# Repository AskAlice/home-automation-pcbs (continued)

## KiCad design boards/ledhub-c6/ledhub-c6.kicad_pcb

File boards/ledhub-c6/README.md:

# ledhub-c6 — all-in-one display LED controller (80 × 50 mm)

ESP32-C6-WROOM-1 based LED controller with 2.8" ILI9341 TFT, EC11 rotary
encoder, 5-way ADC-ladder nav buttons, INMP441 I2S microphone, SHT31 +
BH1750 environmental sensors, LD2450 mmWave radar header, and a 5 V
level-shifted WS2812 output (74AHCT125 + 470 Ω).

**Primary firmware: WLED 0.15+** (ESP32-C6 supported since 0.15) with
`firmware/wled-usermod-ledhub/`. ESPHome is also possible — see
`esphome/ledhub-c6.yaml` (draft covering display, encoder, ADC buttons,
I2S mic, I2C sensors, LD2450 UART, RMT LED strip).

License: MIT. KiCad 8 project, generated by `gen_ledhub_c6.py`
(`python3 gen_ledhub_c6.py`; exits non-zero on any validation problem).

## Features

- USB-C power + native USB-Serial-JTAG flashing (GPIO12/13 via 22 Ω,
  5.1 kΩ CC pull-downs)
- AP2112K-3.3 LDO (VBUS → +3V3), logic 5 V rail `+5V` from VBUS via R20 0R
- Separate `LED_5V` input terminal (J4, 5.08 mm) powering the LED strip
  only; LED data out on J3 (LED_5V / DATA / GND)
- 74AHCT125 (U5, SOIC-14, VCC=+5V, 1OE=GND) level-shifts GPIO3 → LED_DATA
  through R19 470 Ω
- Antenna keepout (no copper, all layers) at the module antenna end

## Frozen pin map (firmware contract — do not change)

| Function | ESP32-C6 GPIO |
|---|---|
| TFT SCK / MOSI / CS / DC / RST / BL | 6 / 7 / 5 / 4 / 1 / 2 |
| Encoder A / B (common = GND; push NC) | 15 / 16 |
| Nav button ladder (ADC1_CH0) | 0 |
| INMP441 I2S SCK / WS / SD (L/R=GND) | 17 / 18 / 19 |
| I2C SDA / SCL (SHT31 + BH1750, 4.7 kΩ) | 20 / 21 |
| LD2450: MCU_RX ← radar TX / MCU_TX → radar RX | 22 / 23 |
| WS2812 data (via 74AHCT125) | 3 |
| USB D− / D+ | 12 / 13 |
| UART0 TX0 / RX0 (prog header J5) | 16 / 17 |
| BOOT button / EN reset | 9 / EN |

GPIO 8/9/12/13/26–30 avoided for general I/O (strapping/USB/flash).

## GPIO16/17 double-assignment — R16/R17 0Ω links

The frozen pin map uses GPIO16 for both ENC_B and UART0 TX0, and GPIO17
for both I2S_SCK and UART0 RX0. R16 (ENC_B↔TX0) and R17 (I2S_SCK↔RX0)
are 0 Ω links, fitted by default. **Flash firmware via native USB-C**
(USB-Serial-JTAG on GPIO12/13) — no UART adapter needed. For classic
UART0 flashing via J5, remove R16/R17 (or accept encoder/I2S contention
while the programmer is attached). Documented on the schematic (title
block notes) and here.

## ADC button ladder (GPIO0, 12-bit)

Topology: +3V3 —10 kΩ (R11)— GPIO0 node; each button shorts the node to
GND through its ladder resistor:

| Button | R | Voltage | ADC (0–4095) | Threshold band |
|---|---|---|---|---|
| UP | 0 Ω (R12) | 0.000 V | 0 | < 369 |
| DN | 2.2 kΩ (R13) | 0.595 V | 738 | 369–1023 |
| LF | 4.7 kΩ (R14) | 1.055 V | 1308 | 1023–1678 |
| RT | 10 kΩ (R15) | 1.650 V | 2048 | 1678–2430 |
| OK | 22 kΩ (R18) | 2.269 V | 2813 | 2430–3454 |
| none | — | 3.300 V | 4095 | > 3454 |

## BOM (bom_lcsc.csv; LCSC numbers verified in-stock via jlcsearch, 2026-08)

| Ref | Value | Footprint | LCSC # | MPN | Qty |
|---|---|---|---|---|---|
| U1 | ESP32-C6-WROOM-1 | custom 18×25.5 mm | C5366877 | ESP32-C6-WROOM-1-N8 | 1 |
| X1 | USB-C 16P receptacle | USB_C_Receptacle_USB2.0_16P | C165948 | TYPE-C-31-M-12 | 1 |
| U2 | INMP441 (bottom port) | custom LGA-9 | — (not stocked) | INMP441ACEZ-R7 | 1 |
| U3 | SHT31 | custom DFN-8 2.5×2.5 | C80862 | SHT31-DIS-B2.5kS | 1 |
| U4 | BH1750 | custom WSOF-6I | C78960 | BH1750FVI-TR | 1 |
| U5 | 74AHCT125 | SOIC-14 | C842299 | 74AHCT125S14-13 | 1 |
| U6 | AP2112K-3.3 | SOT-23-5 | C51118 | AP2112K-3.3TRG1 | 1 |
| ENC1 | EC11 encoder | custom THT | C370970 | EC11E15244G1 | 1 |
| R1,R2,R14 | 4.7 kΩ | 0603 | C23162 | 0603WAF4701T5E | 3 |
| R13 | 2.2 kΩ | 0603 | C4190 | 0603WAF2201T5E | 1 |
| R7,R10,R11,R15 | 10 kΩ | 0603 | C25804 | 0603WAF1002T5E | 4 |
| R18 | 22 kΩ | 0603 | C31850 | 0603WAF2202T5E | 1 |
| R3,R4 | 5.1 kΩ | 0603 | C23186 | 0603WAF5101T5E | 2 |
| R5,R6 | 22 Ω | 0603 | C22926 | 0603WAF220JT5E | 2 |
| R9 | 100 Ω | 0603 | C22775 | 0603WAF1000T5E | 1 |
| R19 | 470 Ω | 0603 | C23179 | 0603WAF4700T5E | 1 |
| R8 | 1 kΩ | 0603 | C21190 | 0603WAF1001T5E | 1 |
| R12,R16,R17,R20,R21 | 0 Ω link | 0603 | C21189 | 0603WAF0000T5E | 5 |
| C1,C2,C8 | 10 µF | 0603 | C15849 | CL10A106KP8NNNC | 3 |
| C3–C7,C9,C10 | 100 nF | 0603 | C14663 | 0603B104K500NT | 7 |
| D1 | red LED | 0603 | C2286 | LTST-C190KRKT | 1 |
| BT1,BT2,BT_UP/DN/LF/RT/OK | tactile 6×6 | custom SMD | C318884 | TS-1187A-B-A-B | 7 |
| J1 | 2×7 header (TFT) | PinHeader_2x07 | C492424 | PZ254V-12-14P | 1 |
| J2 | 1×5 header (LD2450) | PinHeader_1x05 | C492404 | PZ254V-11-05P | 1 |
| J5 | 1×4 header (prog) | PinHeader_1x04 | C2691448 | PZ254V-11-04P | 1 |
| J3 | screw terminal 3P | custom KF128-5.08 | C474953 | KF128-5.08-3P-AA | 1 |
| J4 | screw terminal 2P | custom KF128-5.08 | C474952 | KF128-5.08-2P-AA | 1 |
| (on J1) | 2.8" ILI9341 TFT module | module | — | ILI9341-2.8-SPI | 1 |
| (on J2) | LD2450 radar module | module | — | HLK-LD2450 | 1 |

## Assembly / mechanical notes

- **INMP441 (U2)** is a bottom-port LGA (4.72×3.76 mm): the PCB has an
  Ø0.8 mm sound-port hole under the package. Reflow strongly
  recommended; hand-soldering is hostile (no exposed pad edges). Do not
  plug the port hole with solder.
- **SHT31** footprint is the real DFN-8 2.5×2.5 mm package.
- **TFT module** on J1 (2×7 header) may overhang the board edge —
  mechanical note only; confirm clearance in the enclosure.
- EC11 switch pins are NC (push = use OK button instead).
- TFT backlight: GPIO2 via R9 100 Ω, R10 10 kΩ pull-down keeps the
  backlight off during reset.

## Routing status

Rev 1.0 ships with **no routed tracks/vias**: all nets are ratsnest
(a full-board GND pour on B.Cu plus small per-net marker pours on F.Cu
document the net set). A previous auto-routing attempt produced cross-net
collisions, so routing is deliberately deferred to interactive work in
KiCad (or a verified autorouter pass). Power rails must be routed at
≥ 0.5 mm when done. The generator self-checks pad/courtyard clearances
geometrically and the kicad-happy analyzer reports **0 cross-net
(DFM-001) violations**.

## Analyzer notes (kicad-happy triage)

- PM-002 BT1/BT2 0.75 mm from board edge: intentional (left-edge button
  column); >= 0.5 mm fab clearance held.
- TE-001 no test points: prog header J5 + module pads serve as access.
- TV-001 no thermal vias on U1 EP: EP is ground-paddle soldered;
  C6 module dissipation is modest; add via-in-pad if thermals matter.
- PU-001 SHT31 ALERT/RESET NC by design (not used).
- RS-001 +5V/LED_5V/VBUS "no declared source": rails enter via USB-C /
  screw terminals (connectors are the sources).
- DS-002: datasheets/ sync is handled by the repo-level parts pipeline.

## Flashing

1. Hold BOOT (BT2), tap EN (BT1), release BOOT → download mode.
2. `esptool.py --chip esp32c6 write_flash ...` via the USB-C port
   (native USB-Serial-JTAG), or `esphome run esphome/ledhub-c6.yaml`.
3. UART0 header J5 (+3V3/TX0/RX0/GND) only with R16/R17 removed.

**Verify all custom footprints against the manufacturer datasheets before
fabrication.** Renders: see below (`render_top.png` / `render_bottom.png`
when generated by `tools/render_pcb.py`).

## Renders

| Raytraced 3D (KiCad) | 2D layout |
|---|---|
|  |  |
|  |  |

🎬 24 real KiCad raytraced frames
stitched with ffmpeg (`tools/turntable.sh`).

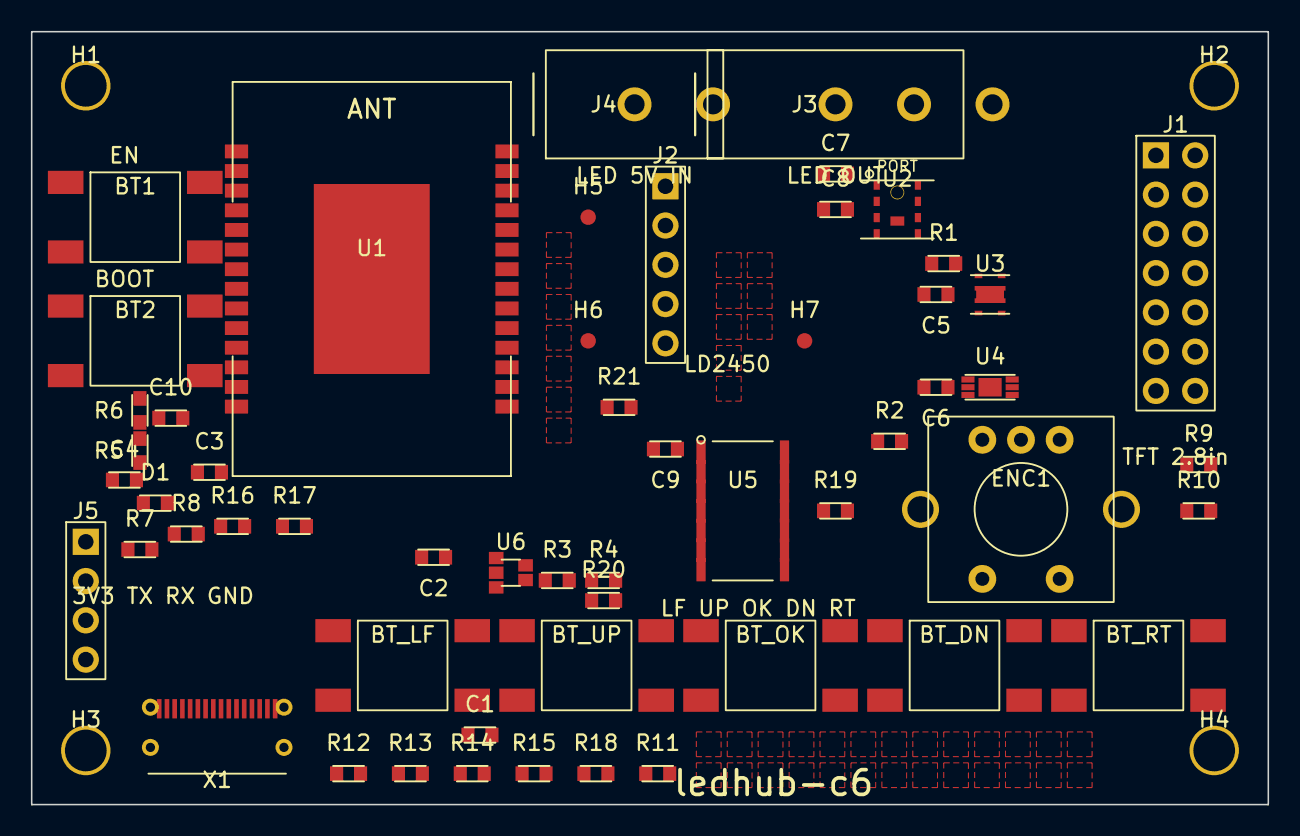
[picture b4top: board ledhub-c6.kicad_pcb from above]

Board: 2 copper layers, 80.0 x 50.0 mm, 59 parts (0 on the bottom side), 37 nets, no tracks yet.

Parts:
BT1, BT2: SW_PUSH; Tactile-6x6-SMD
BT_DN: SW_PUSH; Tactile-6x6-SMD
BT_LF: SW_PUSH; Tactile-6x6-SMD
BT_OK: SW_PUSH; Tactile-6x6-SMD
BT_RT: SW_PUSH; Tactile-6x6-SMD
BT_UP: SW_PUSH; Tactile-6x6-SMD
C1, C2, C8: 10uF; C_0603_1608Metric
C3, C4, C5, C6, C7, C9, C10: 100nF; C_0603_1608Metric
D1: LED_RED; LED_0603_1608Metric
ENC1: EC11; EC11-Encoder
H1, H2, H3, H4: MountingHole_M2.5
H5, H6, H7: Fiducial; Fiducial_1mm
J1: Conn_02x07; PinHeader_2x07_P2.54mm_Vertical
J2: Conn_01x05; PinHeader_1x05_P2.54mm_Vertical
J3: Term_3P; KF128-5.08-3P
J4: Term_2P; KF128-5.08-2P
J5: Conn_01x04; PinHeader_1x04_P2.54mm_Vertical
R1, R2, R14: 4.7k; R_0603_1608Metric
R3, R4: 5.1k; R_0603_1608Metric
R5, R6: 22R; R_0603_1608Metric
R7, R10, R11, R15: 10k; R_0603_1608Metric
R8: 1k; R_0603_1608Metric
R9: 100R; R_0603_1608Metric
R12, R16, R17, R20, R21: 0R; R_0603_1608Metric
R13: 2.2k; R_0603_1608Metric
R18: 22k; R_0603_1608Metric
R19: 470R; R_0603_1608Metric
U1: ESP32-C6-WROOM-1
U2: INMP441; INMP441-LGA9
U3: SHT31; SHT31-DFN8
U4: BH1750; BH1750-WSOF6
U5: 74AHCT125; SOIC-14_3.9x8.7mm_P1.27mm
U6: AP2112K-3.3; SOT-23-5
X1: USB_C_16P; USB_C_Receptacle_USB2.0_16P

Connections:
+3V3: C2.1, C3.1, C5.1, C6.1, C7.1, C8.1, C10.1, J1.1, J5.1, R1.1, R2.1, R7.1, R8.1, R11.1, U1.2, U2.7, U2.8, U3.5, U4.1, U4.5, U6.5
+5V: C9.1, J2.1, R20.2, U5.4, U5.10, U5.13, U5.14
BTN_ADC: R11.2, R12.1, R13.1, R14.1, R15.1, R18.1, U1.8
B_OK: BT1.1, BT1.3, BT2.1, BT2.3, BT_DN.1, BT_DN.3, BT_LF.1, BT_LF.3, BT_OK.1, BT_OK.3, BT_RT.1, BT_RT.3, BT_UP.1, BT_UP.3, R18.2
EN: C4.1, R7.2, U1.3
ENC_A: ENC1.1, U1.23
ENC_B: ENC1.3, R16.1, U1.25
GND: BT1.2, BT1.4, BT2.2, BT2.4, BT_DN.2, BT_DN.4, BT_LF.2, BT_LF.4, BT_OK.2, BT_OK.4, BT_RT.2, BT_RT.4, BT_UP.2, BT_UP.4, C1.2, C2.2, C3.2, C4.2, C5.2, C6.2, C7.2, C8.2, C9.2, C10.2, D1.2, ENC1.2, J1.2, J2.4, J2.5, J3.3, J4.2, J5.4, R3.2, R4.2, R10.2, U1.1, U1.28, U1.29, U2.4, U2.5, U2.6, U2.9, U3.2, U3.8, U3.9, U4.2, U4.3, U4.7, U5.1, U5.5, U5.7, U5.9, U5.12, U6.2, X1.1, X1.8, X1.9, X1.16, X1.S1, X1.S2, X1.S3, X1.S4
I2C_SCL: R2.2, U1.19, U3.4, U4.6
I2C_SDA: R1.2, U1.18, U3.1, U4.4
I2S_SCK: R17.1, U1.24, U2.1
I2S_SD: U1.17, U2.2
I2S_WS: U1.16, U2.3
LED1_A: D1.1, R8.2
LED_5V: J3.1, J4.1
LED_DATA: J3.2, R19.2
LED_DIN: R21.1, U1.26
LED_DINB: R21.2, U5.2
LED_PRE: R19.1, U5.3
RAD_RX: J2.2, U1.20
RAD_TX: J2.3, U1.21
RX0: J5.3, R17.2
TFT_BL: R9.1, U1.27
TFT_BLP: J1.8, R9.2, R10.1
TFT_CS: J1.3, U1.5
TFT_DC: J1.5, U1.4
TFT_MOSI: J1.6, U1.7
TFT_RST: J1.4, U1.9
TFT_SCK: J1.7, U1.6
TX0: J5.2, R16.2
USB_CC1: R3.1, X1.3
USB_CC2: R4.1, X1.14
USB_DM: R6.2, U1.13
USB_DM_CON: R6.1, X1.5, X1.12
USB_DP: R5.2, U1.14
USB_DP_CON: R5.1, X1.4, X1.13
VBUS: C1.1, R20.1, U6.1, U6.3, X1.2, X1.7, X1.10, X1.15

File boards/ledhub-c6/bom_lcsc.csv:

ref,value,footprint,lcsc,mpn,qty
U1,ESP32-C6-WROOM-1,custom:ESP32-C6-WROOM-1,C5366877,ESP32-C6-WROOM-1-N8,1
X1,USB_C_16P,Connector_USB:USB_C_Receptacle_USB2.0_16P,C165948,TYPE-C-31-M-12,1
U2,INMP441,custom:INMP441-LGA9,-,INMP441ACEZ-R7,1
U3,SHT31,custom:SHT31-DFN8,C80862,SHT31-DIS-B2.5kS,1
U4,BH1750,custom:BH1750-WSOF6,C78960,BH1750FVI-TR,1
U5,74AHCT125,Package_SO:SOIC-14_3.9x8.7mm_P1.27mm,C842299,74AHCT125S14-13,1
U6,AP2112K-3.3,Package_TO_SOT_SMD:SOT-23-5,C51118,AP2112K-3.3TRG1,1
ENC1,EC11,custom:EC11-Encoder,C370970,EC11E15244G1,1
R1,R2,R14,4.7k,Resistor_SMD:R_0603_1608Metric,C23162,0603WAF4701T5E,3
R13,2.2k,Resistor_SMD:R_0603_1608Metric,C4190,0603WAF2201T5E,1
R7,R10,R11,R15,10k,Resistor_SMD:R_0603_1608Metric,C25804,0603WAF1002T5E,4
R18,22k,Resistor_SMD:R_0603_1608Metric,C31850,0603WAF2202T5E,1
R3,R4,5.1k,Resistor_SMD:R_0603_1608Metric,C23186,0603WAF5101T5E,2
R5,R6,22R,Resistor_SMD:R_0603_1608Metric,C22926,0603WAF220JT5E,2
R9,100R,Resistor_SMD:R_0603_1608Metric,C22775,0603WAF1000T5E,1
R19,470R,Resistor_SMD:R_0603_1608Metric,C23179,0603WAF4700T5E,1
R8,1k,Resistor_SMD:R_0603_1608Metric,C21190,0603WAF1001T5E,1
R12,R16,R17,R20,R21,0R,Resistor_SMD:R_0603_1608Metric,C21189,0603WAF0000T5E,5
C1,C2,C8,10uF,Capacitor_SMD:C_0603_1608Metric,C15849,CL10A106KP8NNNC,3
C3,C4,C5,C6,C7,C9,C10,100nF,Capacitor_SMD:C_0603_1608Metric,C14663,0603B104K500NT,7
D1,LED_RED,LED_SMD:LED_0603_1608Metric,C2286,LTST-C190KRKT,1
BT1,BT2,BT_UP,BT_DN,BT_LF,BT_RT,BT_OK,SW_PUSH,custom:Tactile-6x6-SMD,C318884,TS-1187A-B-A-B,7
J1,Conn_02x07,Connector_PinHeader_2.54mm:PinHeader_2x07_P2.54mm_Vertical,C492424,PZ254V-12-14P,1
J2,Conn_01x05,Connector_PinHeader_2.54mm:PinHeader_1x05_P2.54mm_Vertical,C492404,PZ254V-11-05P,1
J5,Conn_01x04,Connector_PinHeader_2.54mm:PinHeader_1x04_P2.54mm_Vertical,C2691448,PZ254V-11-04P,1
J3,Term_3P,custom:KF128-5.08-3P,C474953,KF128-5.08-3P-AA,1
J4,Term_2P,custom:KF128-5.08-2P,C474952,KF128-5.08-2P-AA,1
(on J2),LD2450,-,-,HLK-LD2450,1
(on J1),TFT_2.8,-,-,ILI9341-2.8-SPI,1

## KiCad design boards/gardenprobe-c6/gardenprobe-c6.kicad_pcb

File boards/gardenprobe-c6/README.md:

# gardenprobe-c6 — battery soil-moisture stick node (SPEC 7.5)

ESP32-C6-WROOM-1 soil-probe node: 70 × 25 mm stick with capacitive copper
probe area on the B.Cu tip (J2), JST-PH LiPo input, MCP1700-3302 LDO,
AO3401 sensor-rail load switch, SHT31 temp/humidity, battery divider.
**v0.1 concept board.**

- Board: 70 × 25 mm, 2-layer; antenna keep-out along left edge; probe tip right
- Power: 3.7 V LiPo on JST-PH (BT1) — **charge externally, no charger on board**
- Status: `python3 boards/wave2/wave2gen.py gardenprobe-c6` → self-check OK

## BOM (bom_lcsc.csv)

| Ref | Value | Footprint | LCSC # | MPN | Qty |
|---|---|---|---|---|---|
| U1 | ESP32-C6-WROOM-1 (rot 270°) | ESP32-C6-WROOM-1 | C2946979 | ESP32-C6-WROOM-1-N8 | 1 |
| U2 | MCP1700-3302E | SOT-23 | C63395 | MCP1700T-3302E/TT | 1 |
| U3 | SHT31-DIS | custom:SHT31-DFN8 | C23324 | SHT31-DIS-B2.5kS | 1 |
| Q1 | AO3401 (load switch) | SOT-23 | C15127 | AO3401A | 1 |
| BT1 | JST-PH 2P (LiPo) | custom:JST-PH-S2B | C265758 | S2B-PH-K-S | 1 |
| J2 | SoilProbe electrodes | custom:SoilProbe-BCu | — | copper area on B.Cu (ENIG rec.) | 1 |
| R1,R4 | 100k (battery divider) | 0603 | C98258 | 0603WAF1003T5E | 2 |
| R5 | 1M (soil charge) | 0603 | C22935 | 0603WAF1004T5E | 1 |
| R3 | 10k (load-switch gate) | 0603 | C98252 | 0603WAF1002T5E | 1 |
| R6,R7 | 4.7k (I2C pull-ups, switched) | 0603 | C23162 | 0603WAF4701T5E | 2 |
| C1,C2,C3,C4 | 100nF | 0603 | C14663 | CL10B104KB8NNNC | 4 |
| J1 | Conn_01x04 (3V3/TX0/RX0/GND) | PinHeader_1x04_P2.54mm | C49241 | A2541WV-4P | 1 |

## Pinout (C6-WROOM-1)

| Signal | GPIO | Notes |
|---|---|---|
| SOIL_ADC | GPIO0 | probe sense via R5 1M from GPIO1 (fixed-RC) |
| SOIL_CHG | GPIO1 | charge/drive pin for probe |
| BATT_ADC | GPIO2 | 100k/100k divider → Vbat/2 |
| LOAD_EN | GPIO3 | Q1 AO3401 → +3V3_SW (SHT31 + I2C pull-ups) |
| I2C_SDA / I2C_SCL | GPIO20 / GPIO21 | U3 SHT31 (0x44), pull-ups on switched rail |
| TX0 / RX0 | GPIO16 / GPIO17 | J1 prog header (flash via UART; no USB) |
| EN | — | pull-up + C2 |

## Firmware

See `esphome/gardenprobe-c6.yaml` — load-switch GPIO3, sht3xd on switched
I2C, ADC soil raw (GPIO0) + battery (GPIO2, ×2), deep-sleep 30 min cycles.
Calibrate soil raw → % per installation.

## Routing status

**v0.1 concept — signals left for autorouting.** Power rails routed
(VBAT/+3V3/+3V3_SW/GND + stitching); ADC/I2C/UART/enable signals unrouted.

## Analyzer notes

`analyze_pcb.py`: **DFM-001 = 0**. RT-001 unrouted errors expected.
SHT31 DFN-8 EP resized (1.4×1.0) to clear the 1.05 mm pad columns.

## Caveats (verify before fabrication!)

- No battery charger on board — LiPo must be charged externally; consider
  adding protection (DW01) for production.
- Probe electrodes are bare B.Cu — specify ENIG or immersion-gold finish;
  HASL/copper will corrode in soil quickly.
- MCP1700 Iq ~1.6 µA suits sleep; verify divider current budget (100k/100k
  ≈ 21 µA at 4.2 V — the dominant sleep draw; raise values if needed).
- **Verify all footprints, pin numbers, and clearances against KiCad
  libraries + datasheets before ordering boards.**

## Renders

| Raytraced 3D (KiCad) | 2D layout |
|---|---|
|  |  |
|  |  |

🎬 24 real KiCad raytraced frames stitched with ffmpeg (tools/turntable.sh).

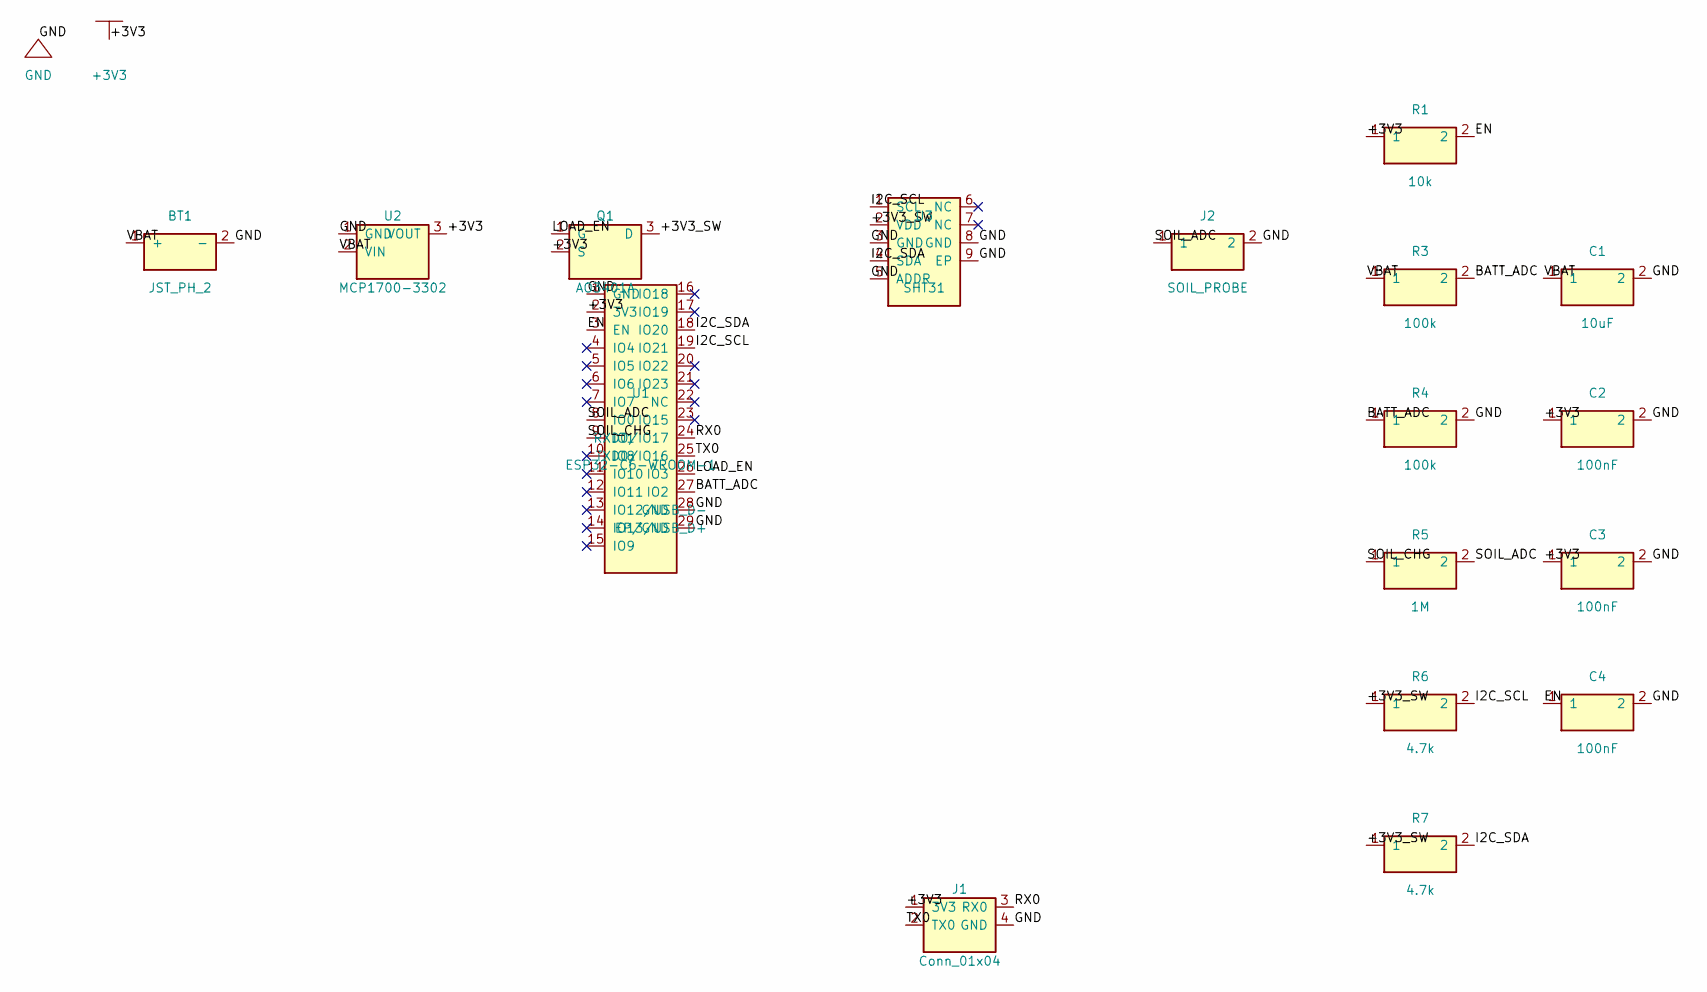
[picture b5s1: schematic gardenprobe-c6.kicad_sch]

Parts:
BT1: JST_PH_2; JST-PH-2; LCSC C131337
C1: 10uF; C_0603_1608Metric; LCSC C15849
C2, C3, C4: 100nF; C_0603_1608Metric; LCSC C14663
J1: Conn_01x04; PinHeader_1x04_P2.54mm_Vertical; LCSC C49258
J2: SOIL_PROBE; SoilProbe-BCu; LCSC —
Q1: AO3401A; SOT-23; LCSC C15127
R1: 10k; R_0603_1608Metric; LCSC C25804
R3, R4: 100k; R_0603_1608Metric; LCSC C25803
R5: 1M; R_0603_1608Metric; LCSC C269433
R6, R7: 4.7k; R_0603_1608Metric; LCSC C23162
U1: ESP32-C6-WROOM-1; LCSC C5366877
U2: MCP1700-3302; SOT-23; LCSC C39051
U3: SHT31; SHT31-DFN8; LCSC C80862

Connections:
+3V3: C2.1, C3.1, J1.1 (3V3), Q1.2 (S), R1.1, U1.2 (3V3), U2.3 (VOUT)
+3V3_SW: Q1.3 (D), R6.1, R7.1, U3.2 (VDD)
BATT_ADC: R3.2, R4.1, U1.27 (IO2)
EN: C4.1, R1.2, U1.3 (EN)
GND: BT1.2 (-), C1.2, C2.2, C3.2, C4.2, J1.4 (GND), J2.2, R4.2, U1.1 (GND), U1.28 (GND), U1.29 (EP/GND), U2.1 (GND), U3.3 (GND), U3.5 (ADDR), U3.8 (GND), U3.9 (EP)
I2C_SCL: R6.2, U1.19 (IO21), U3.1 (SCL)
I2C_SDA: R7.2, U1.18 (IO20), U3.4 (SDA)
LOAD_EN: Q1.1 (G), U1.26 (IO3)
RX0: J1.3 (RX0), U1.24 (RXD0/IO17)
SOIL_ADC: J2.1, R5.2, U1.8 (IO0)
SOIL_CHG: R5.1, U1.9 (IO1)
TX0: J1.2 (TX0), U1.25 (TXD0/IO16)
VBAT: BT1.1 (+), C1.1, R3.1, U2.2 (VIN)

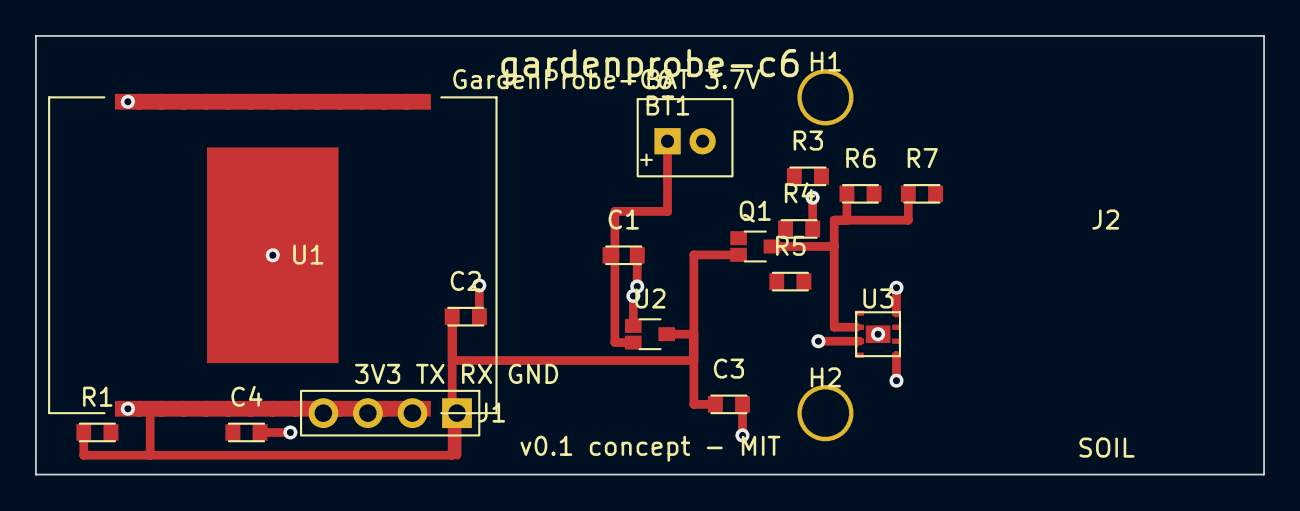
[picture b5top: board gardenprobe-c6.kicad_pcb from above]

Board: 2 copper layers, 70.0 x 25.0 mm, 19 parts (0 on the bottom side), 13 nets.

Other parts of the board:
H1, H2: MountingHole_M2.5

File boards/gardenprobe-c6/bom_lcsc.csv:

ref,value,footprint,lcsc,mpn,qty
U1,ESP32-C6-WROOM-1,gardenprobe-c6:ESP32-C6-WROOM-1,C5366877,ESP32-C6-WROOM-1-N8,1
BT1,JST_PH_2,gardenprobe-c6:JST-PH-2,C131337,B2B-PH-K-S(LF)(SN),1
U2,MCP1700-3302,Package_TO_SOT_SMD:SOT-23,C39051,MCP1700T-3302E/TT,1
Q1,AO3401A,Package_TO_SOT_SMD:SOT-23,C15127,AO3401A,1
U3,SHT31,gardenprobe-c6:SHT31-DFN8,C80862,SHT31-DIS-B2.5kS,1
J2,SOIL_PROBE,gardenprobe-c6:SoilProbe-BCu,—,copper electrodes on B.Cu (ENIG recommended),1
R1,10k,Resistor_SMD:R_0603_1608Metric,C25804,0603WAF1002T5E,1
R3,R4,100k,Resistor_SMD:R_0603_1608Metric,C25803,0603WAF1003T5E,2
R5,1M,Resistor_SMD:R_0603_1608Metric,C269433,RMC06031M5%N,1
R6,R7,4.7k,Resistor_SMD:R_0603_1608Metric,C23162,0603WAF4701T5E,2
C1,10uF,Capacitor_SMD:C_0603_1608Metric,C15849,CL10A106KP8NNNC,1
C2,C3,C4,100nF,Capacitor_SMD:C_0603_1608Metric,C14663,0603B104K500NT,3
J1,Conn_01x04,Connector_PinHeader_2.54mm:PinHeader_1x04_P2.54mm_Vertical,C49258,KH-2.54PH180-1X4P-L13.5,1

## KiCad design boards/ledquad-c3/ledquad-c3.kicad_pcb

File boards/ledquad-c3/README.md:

# ledquad-c3 — 4-ch 12–24 V PWM LED strip driver (50 × 40 mm)

ESP32-C3-WROOM-02 based 4-channel (RGBW) low-side PWM LED strip driver.
12–24 V in on J1 (5.08 mm screw terminal, fused), AP63205 buck → +5V/2 A,
AP2112K-3.3 LDO → +3V3 logic, 4× AO3400A N-MOSFET output stages, USB-C
programming with SS34 diode-OR between VBUS and the buck 5 V rail.

License: MIT. KiCad 8 project, generated by `gen_ledquad_c3.py`
(`python3 gen_ledquad_c3.py`; exits non-zero on any validation problem).

## Features

- 4× PWM channels, 12–24 V strips: R=GPIO4, G=GPIO5, B=GPIO6, W=GPIO7,
  100 Ω gate resistors + 10 kΩ pull-downs, low-side AO3400A (SOT-23)
- J1: 2-pin 5.08 mm terminal, 12–24 V in; F1 5 A fuse (1206)
- U2 AP63205 buck, fixed 5 V / 2 A (L1 4.7 µH, Cin 10 µF, Cout 2×22 µF,
  BST 100 nF — datasheet typical circuit;
  https://www.diodes.com/assets/Datasheets/AP63205.pdf)
- U3 AP2112K-3.3 LDO for logic
- X1 USB-C 16P programming (5.1 kΩ CC, D+/D− → GPIO19/18 via 22 Ω);
  VBUS diode-OR'd with buck 5 V via D3/D4 (SS34, D_SMA)
- J2: 5-pin 5.08 mm terminal: V+, R, G, B, W (strip connection)
- J3: 1×4 prog header (+3V3 / TX0=GPIO21 / RX0=GPIO20 / GND)
- BT1 EN reset, BT2 BOOT (GPIO9); D1 power LED, D2 status LED (GPIO10)
- Antenna keepout (no copper, all layers), 3 assembly fiducials,
  GND pour on B.Cu

WLED-compatible pin header: J2's V+/R/G/B/W pinout matches common RGBW
screw-terminal strips; the pin map (GPIO4–7) is usable from WLED builds
with a custom LED output config.

## Pinout

| Function | ESP32-C3 GPIO |
|---|---|
| PWM R / G / B / W | 4 / 5 / 6 / 7 |
| Status LED D2 | 10 |
| BOOT button BT2 | 9 |
| USB D− / D+ | 18 / 19 |
| UART0 TX0 / RX0 (J3) | 21 / 20 |
| EN reset BT1 | EN |

J1: pin 1 = VIN (12–24 V +), pin 2 = GND.
J2: pin 1 = V+ (VIN), pins 2–5 = R/G/B/W (switched low side).
J3: pin 1 = +3V3, pin 2 = TX0 (GPIO21), pin 3 = RX0 (GPIO20), pin 4 = GND.

## BOM

See `bom_lcsc.csv` (machine-readable, grouped by part type).

| Ref | Value | Footprint | LCSC | MPN | Qty |
|---|---|---|---|---|---|
| U1 | ESP32-C3-WROOM-02 | custom | C2934560 | ESP32-C3-WROOM-02-N4 | 1 |
| X1 | USB-C 16P | USB_C_Receptacle_USB2.0_16P | C165948 | TYPE-C-31-M-12 | 1 |
| U2 | AP63205 buck 5V/2A | SOT-23-6 | C2071056 | AP63205WU-7 | 1 |
| U3 | AP2112K-3.3 LDO | SOT-23-5 | C51115 | AP2112K-3.3TRG1 | 1 |
| Q1–Q4 | AO3400A N-MOSFET | SOT-23 | C20917 | AO3400A | 4 |
| D3, D4 | SS34 Schottky | D_SMA | C8678 | SS34 | 2 |
| F1 | Fuse 5 A | 1206 | C136351 | JFC1206-1500FS | 1 |
| L1 | 4.7 µH inductor | custom 4×4 | C167874 | FNR4030S4R7MT | 1 |
| J1 | Screw terminal 2P 5.08 | custom | C474952 | KF128-5.08-2P-AA | 1 |
| J2 | Screw terminal 5P 5.08 | custom | C42377750 | WJ500V-5.08-05P-14-00A | 1 |
| J3 | Header 1×4 | 2.54 mm | C49258 | KH-2.54PH180-1X4P-L13.5 | 1 |
| BT1, BT2 | Tactile 6×6 SMD | custom | C139797 | TS-1187A-B-A-B | 2 |
| R1–R4 | 100 Ω | 0603 | C22369795 | RCA03100RFLF | 4 |
| R5–R8, R13 | 10 kΩ | 0603 | C25804 | 0603WAF1002T5E | 5 |
| R9, R10 | 5.1 kΩ | 0603 | C23186 | 0603WAF5101T5E | 2 |
| R11, R12 | 22 Ω | 0603 | C22926 | 0603WAF220JT5E | 2 |
| R14, R15 | 1 kΩ | 0603 | C21190 | 0603WAF1001T5E | 2 |
| R16 | 100 kΩ | 0603 | C25803 | 0603WAF1003T5E | 1 |
| C1, C6, C7, C10 | 10 µF | 0603 | C15849 | CL10A106KP8NNNC | 4 |
| C2, C3, C8, C9 | 100 nF | 0603 | C14663 | 0603B104K500NT | 4 |
| C4, C5 | 22 µF | 0805 | C45783 | CL21A226MAQNNNE | 2 |
| D1 | LED red | 0603 | C2286 | LTST-C190KRKT | 1 |
| D2 | LED green | 0603 | C2297 | LTST-C190KGKT | 1 |

## Flashing

1. USB-C: hold BT2 (BOOT), tap BT1 (EN) → ROM USB-Serial-JTAG bootloader
   (GPIO18/19). Flash with ESPHome / esptool.
2. Or J3 + external 3.3 V UART (TX0=GPIO21, RX0=GPIO20).
3. ESPHome yaml: `esphome/ledquad-c3.yaml`.

## Routing status

Hand-routed by the generator with a geometric copper self-check
(0.15 mm clearance + edge/keepout rules). **Copper objects the self-check
flags are automatically removed**, leaving ratsnest instead of colliding
copper; the log is `analysis/pruned_routes.txt`.

Nets with removed copper (fully/partially unrouted — finish in KiCad before
fabrication): **PWM_R/G/B/W (module→gate-resistor drops), OUT_R/OUT_G
(drain→J2 stubs), +3V3, +5V, 5V_BUCK (partial), VBUS, VIN/VIN_EN
(partial), USB_DM/USB_DP and USB_*_CON, STAT_LED, TX0, RX0, GND (some via
stubs — main GND is the B.Cu pour)**. Power path J1→F1→U2→L1 and the
output stages Q1–Q4→J2 are routed.

## Analyzer notes (kicad-happy)

- `SS-001` (schematic, error): BOM MPN-coverage gate — the analyzer does
  not read `bom_lcsc.csv`; all BOM lines carry LCSC + MPN. Allowed gate.
- `RS-001` (warnings): VIN/VBUS/+5V "no declared source" — these are the
  board input / regulator rails, by design.
- `CG-AUD` (warning): J2 5-pin terminal "no ground pins" — intentional;
  J2 is V+ + 4 switched low-side channels (strip GND returns via V+ lead).
- `PM-001`/`PM-002` (warnings): residual small courtyard overlaps
  (≤ ~1 mm²) around the screw terminals / USB-C and J1 0.6 mm→(fixed to
  ≥1 mm edge distance after rework) — terminal bodies intentionally face
  the board edge; copper self-check passes.
- `TE-001`/`TV-001` (warnings): no test points, limited thermal vias —
  accepted for a prototype.
- DFM-001 cross-net violations: **0**. Cross-analysis: 0 findings.
  `validate_project`: pass.

## Fabrication disclaimer

Prototype design generated programmatically. Custom footprints
(ESP32-C3-WROOM-02, L-4x4-4R7, TB-5.08-2P/5P, tactile 6×6) should be
**verified against manufacturer datasheets before fabrication**. Complete
the unrouted nets listed above in KiCad first. No photos yet — renders
(`render_top.png` / `render_bottom.png`) are machine-generated.

## Renders

| Raytraced 3D (KiCad) | 2D layout |
|---|---|
|  |  |
|  |  |

🎬 24 real KiCad raytraced frames stitched with ffmpeg (tools/turntable.sh).

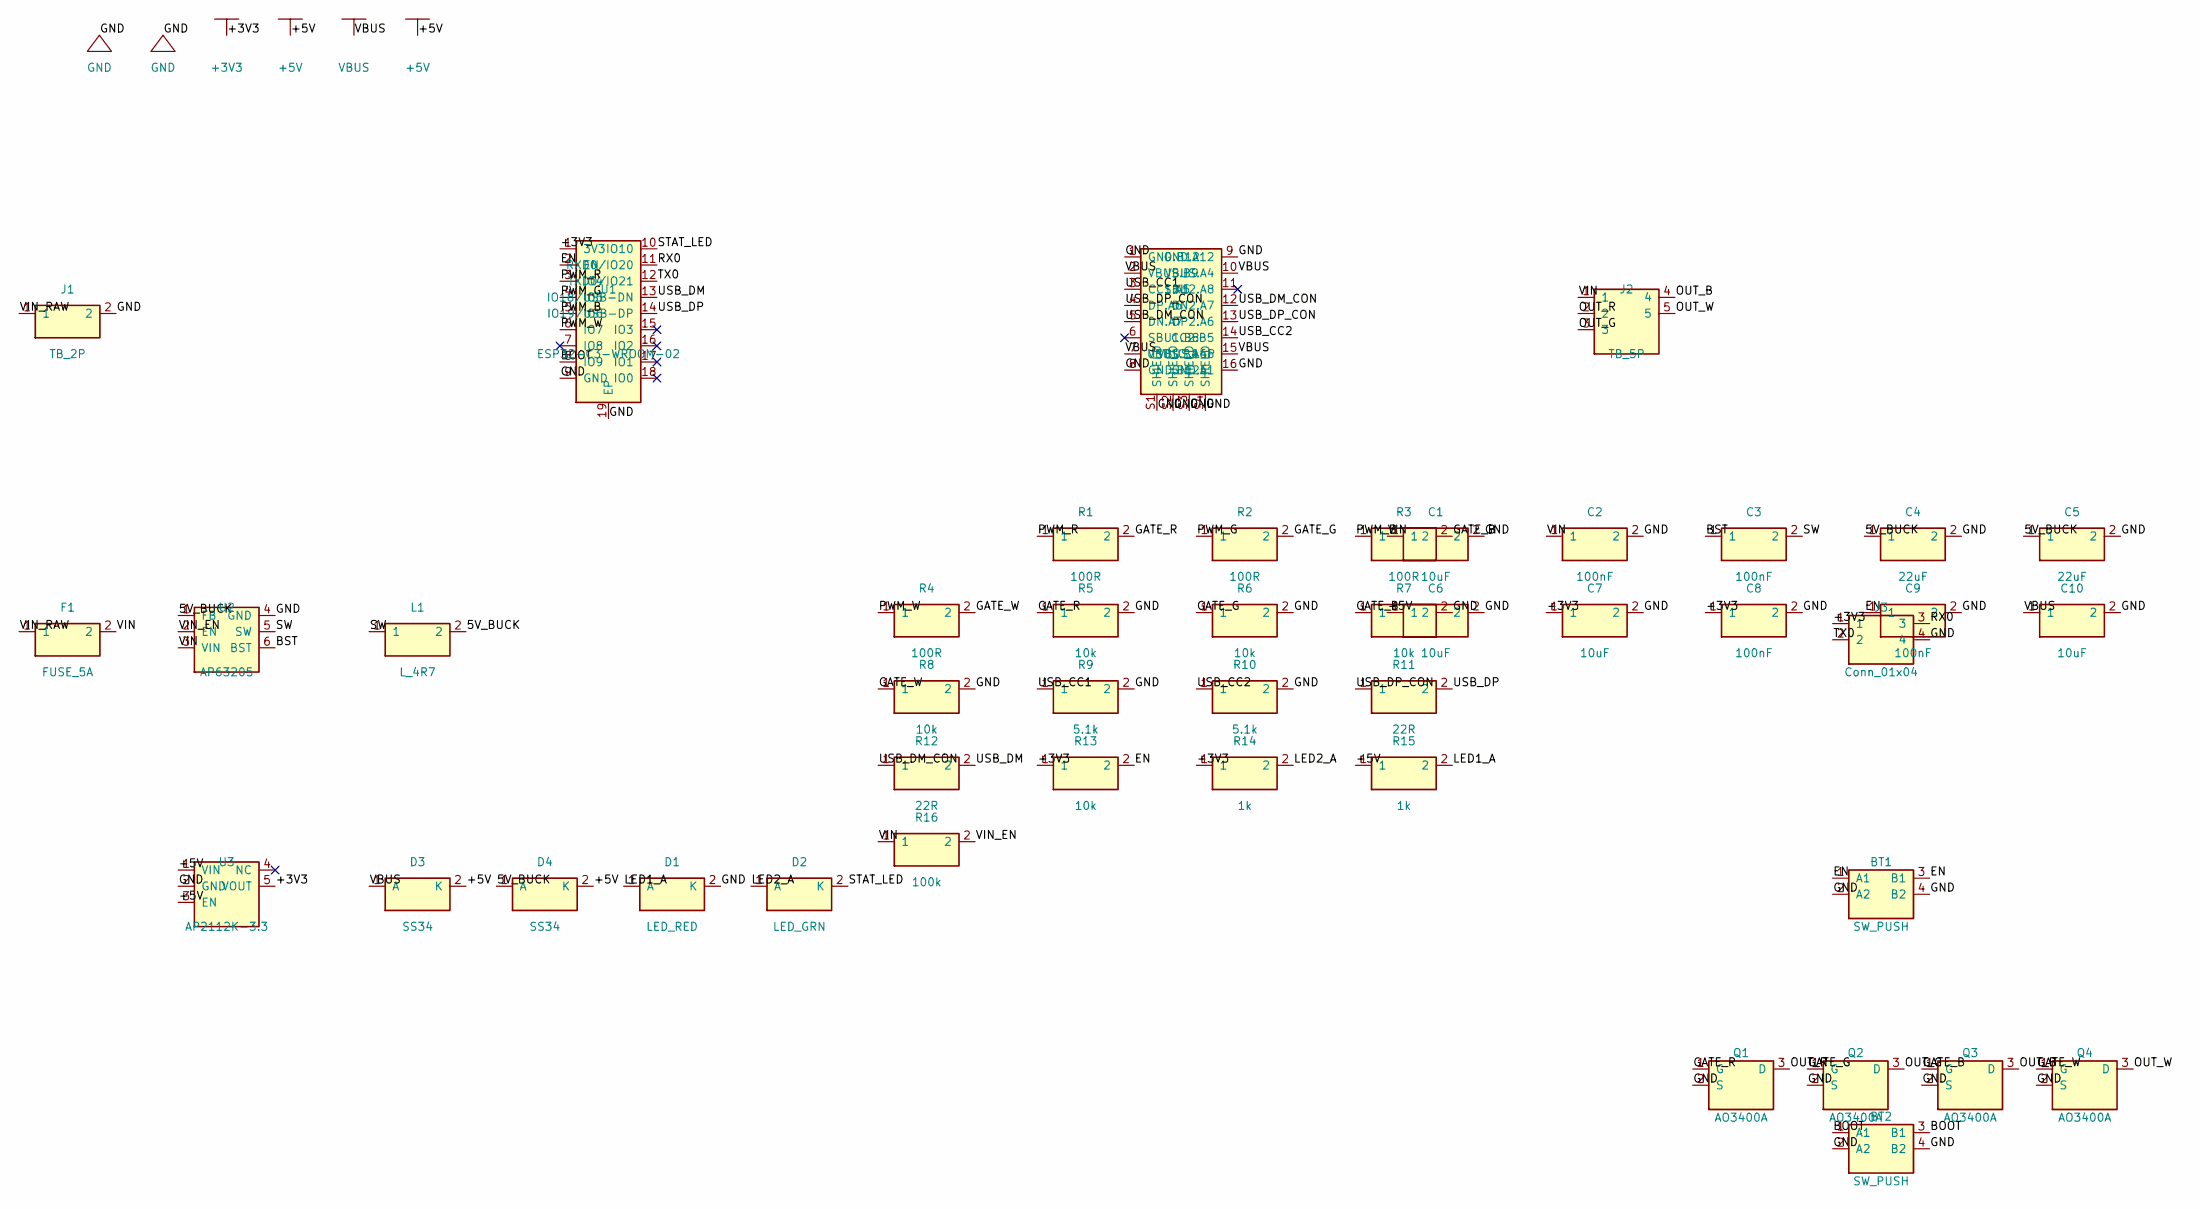
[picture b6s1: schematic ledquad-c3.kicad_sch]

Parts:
BT1, BT2: SW_PUSH; Tactile-6x6-SMD; LCSC C139797
C1, C6, C7, C10: 10uF; C_0603_1608Metric; LCSC C15849
C2, C3, C8, C9: 100nF; C_0603_1608Metric; LCSC C14663
C4, C5: 22uF; C_0805_2012Metric; LCSC C45783
D1: LED_RED; LED_0603_1608Metric; LCSC C2286
D2: LED_GRN; LED_0603_1608Metric; LCSC C2297
D3, D4: SS34; D_SMA; LCSC C8678
F1: FUSE_5A; Fuse_1206_3216Metric; LCSC C136351
J1: TB_2P; TB-5.08-2P; LCSC C474952
J2: TB_5P; TB-5.08-5P; LCSC C42377750
J3: Conn_01x04; PinHeader_1x04_P2.54mm_Vertical; LCSC C49258
L1: L_4R7; L-4x4-4R7; LCSC C167874
Q1, Q2, Q3, Q4: AO3400A; SOT-23; LCSC C20917
R1, R2, R3, R4: 100R; R_0603_1608Metric; LCSC C22369795
R5, R6, R7, R8, R13: 10k; R_0603_1608Metric; LCSC C25804
R9, R10: 5.1k; R_0603_1608Metric; LCSC C23186
R11, R12: 22R; R_0603_1608Metric; LCSC C22926
R14, R15: 1k; R_0603_1608Metric; LCSC C21190
R16: 100k; R_0603_1608Metric; LCSC C25803
U1: ESP32-C3-WROOM-02; LCSC C2934560
U2: AP63205; SOT-23-6; LCSC C2071056
U3: AP2112K-3.3; SOT-23-5; LCSC C51115
X1: USB_C_16P; USB_C_Receptacle_USB2.0_16P; LCSC C165948

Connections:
5V_BUCK: C4.1, C5.1, D4.1 (A), L1.2, U2.1 (FB)
+3V3: C7.1, C8.1, J3.1, R13.1, R14.1, U1.1 (3V3), U3.5 (VOUT)
+5V: C6.1, D3.2 (K), D4.2 (K), R15.1, U3.1 (VIN), U3.3 (EN)
BST: C3.1, U2.6 (BST)
GATE_B: Q3.1 (G), R3.2, R7.1
GATE_G: Q2.1 (G), R2.2, R6.1
GATE_R: Q1.1 (G), R1.2, R5.1
GATE_W: Q4.1 (G), R4.2, R8.1
GND: BT1.2 (A2), BT1.4 (B2), BT2.2 (A2), BT2.4 (B2), C1.2, C2.2, C4.2, C5.2, C6.2, C7.2, C8.2, C9.2, C10.2, D1.2 (K), J1.2, J3.4, Q1.2 (S), Q2.2 (S), Q3.2 (S), Q4.2 (S), R5.2, R6.2, R7.2, R8.2, R9.2, R10.2, U1.9 (GND), U1.19 (EP), U2.4 (GND), U3.2 (GND), X1.1 (GND.B12), X1.8 (GND.B12b), X1.9 (GND.A12), X1.16 (GND.A1), X1.S1 (SHIELD), X1.S2 (SHIELD), X1.S3 (SHIELD), X1.S4 (SHIELD)
LED1_A: D1.1 (A), R15.2
LED2_A: D2.1 (A), R14.2
OUT_B: J2.4, Q3.3 (D)
OUT_G: J2.3, Q2.3 (D)
OUT_R: J2.2, Q1.3 (D)
OUT_W: J2.5, Q4.3 (D)
PWM_B: R3.1, U1.5 (IO6)
PWM_G: R2.1, U1.4 (IO5)
PWM_R: R1.1, U1.3 (IO4)
PWM_W: R4.1, U1.6 (IO7)
RX0: J3.3, U1.11 (RXD0/IO20)
STAT_LED: D2.2 (K), U1.10 (IO10)
SW: C3.2, L1.1, U2.5 (SW)
TX0: J3.2, U1.12 (TXD0/IO21)
USB_CC1: R9.1, X1.3 (CC1.A5)
USB_CC2: R10.1, X1.14 (CC2.B5)
USB_DM: R12.2, U1.13 (IO18/USB-DN)
USB_DM_CON: R12.1, X1.5 (DN.A7), X1.12 (DN2.A7)
USB_DP: R11.2, U1.14 (IO19/USB-DP)
USB_DP_CON: R11.1, X1.4 (DP.A6), X1.13 (DP2.A6)
VBUS: C10.1, D3.1 (A), X1.2 (VBUS.B9), X1.7 (VBUS.B4), X1.10 (VBUS.A4), X1.15 (VBUS.A4b)
VIN: C1.1, C2.1, F1.2, J2.1, R16.1, U2.3 (VIN)
VIN_EN: R16.2, U2.2 (EN)
VIN_RAW: F1.1, J1.1

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
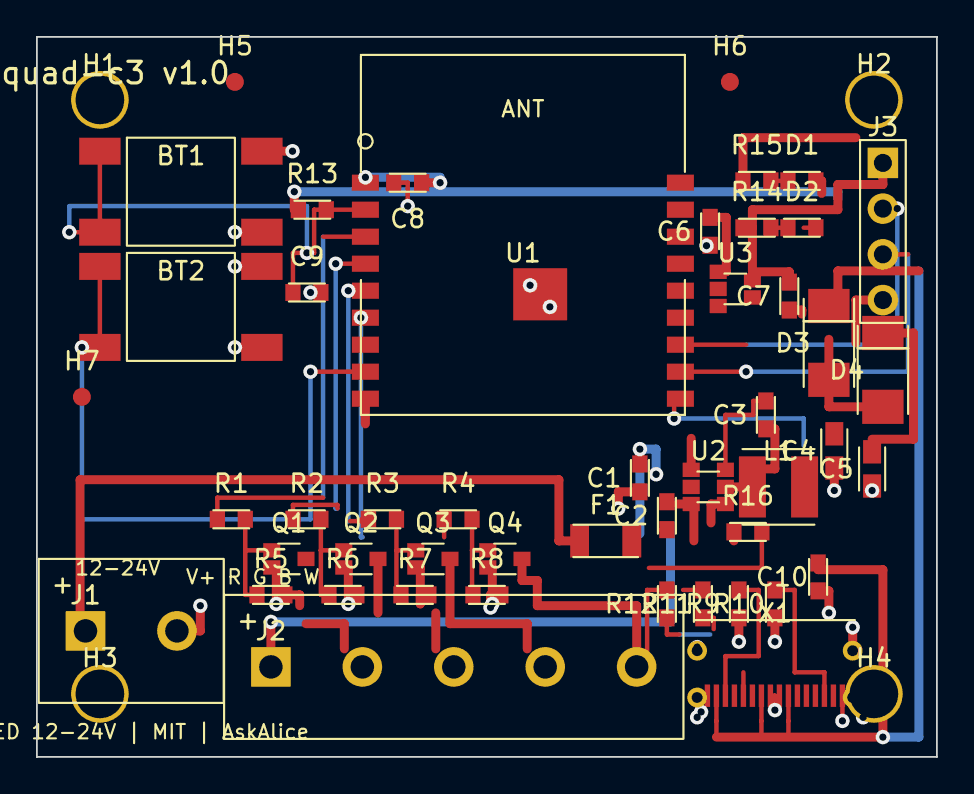
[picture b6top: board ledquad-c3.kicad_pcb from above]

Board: 2 copper layers, 50.0 x 40.0 mm, 52 parts (0 on the bottom side), 35 nets.

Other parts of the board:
H1, H2, H3, H4: MountingHole_M2.5
H5, H6, H7: Fiducial; Fiducial_1mm

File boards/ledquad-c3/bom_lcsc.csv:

ref,value,footprint,lcsc,mpn,qty
U1,ESP32-C3-WROOM-02,custom:ESP32-C3-WROOM-02,C2934560,ESP32-C3-WROOM-02-N4,1
X1,USB_C_16P,Connector_USB:USB_C_Receptacle_USB2.0_16P,C165948,TYPE-C-31-M-12,1
U2,AP63205,Package_TO_SOT_SMD:SOT-23-6,C2071056,AP63205WU-7,1
U3,AP2112K-3.3,Package_TO_SOT_SMD:SOT-23-5,C51115,AP2112K-3.3TRG1,1
Q1,Q2,Q3,Q4,AO3400A,Package_TO_SOT_SMD:SOT-23,C20917,AO3400A,4
D3,D4,SS34,Diode_SMD:D_SMA,C8678,SS34,2
F1,FUSE_5A,Fuse:Fuse_1206_3216Metric,C136351,JFC1206-1500FS,1
L1,L_4R7,custom:L-4x4-4R7,C167874,FNR4030S4R7MT,1
J1,TB_2P,custom:TB-5.08-2P,C474952,KF128-5.08-2P-AA,1
J2,TB_5P,custom:TB-5.08-5P,C42377750,WJ500V-5.08-05P-14-00A,1
J3,Conn_01x04,Connector_PinHeader_2.54mm:PinHeader_1x04_P2.54mm_Vertical,C49258,KH-2.54PH180-1X4P-L13.5,1
BT1,BT2,SW_PUSH,custom:Tactile-6x6-SMD,C139797,TS-1187A-B-A-B,2
R1,R2,R3,R4,100R,Resistor_SMD:R_0603_1608Metric,C22369795,RCA03100RFLF,4
R5,R6,R7,R8,R13,10k,Resistor_SMD:R_0603_1608Metric,C25804,0603WAF1002T5E,5
R9,R10,5.1k,Resistor_SMD:R_0603_1608Metric,C23186,0603WAF5101T5E,2
R11,R12,22R,Resistor_SMD:R_0603_1608Metric,C22926,0603WAF220JT5E,2
R14,R15,1k,Resistor_SMD:R_0603_1608Metric,C21190,0603WAF1001T5E,2
R16,100k,Resistor_SMD:R_0603_1608Metric,C25803,0603WAF1003T5E,1
C1,C6,C7,C10,10uF,Capacitor_SMD:C_0603_1608Metric,C15849,CL10A106KP8NNNC,4
C2,C3,C8,C9,100nF,Capacitor_SMD:C_0603_1608Metric,C14663,0603B104K500NT,4
C4,C5,22uF,Capacitor_SMD:C_0805_2012Metric,C45783,CL21A226MAQNNNE,2
D1,LED_RED,LED_SMD:LED_0603_1608Metric,C2286,LTST-C190KRKT,1
D2,LED_GRN,LED_SMD:LED_0603_1608Metric,C2297,LTST-C190KGKT,1

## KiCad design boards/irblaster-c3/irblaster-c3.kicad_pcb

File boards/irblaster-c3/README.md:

# irblaster-c3 — IR climate bridge (SPEC 7.4)

ESP32-C3-WROOM-02 IR blaster/receiver: 2× TSAL6200 driven by an S8050 from
GPIO4, TSOP38238 receiver on GPIO5, optional BH1750 lux sensor on I2C.
**v0.1 concept board.**

- Board: 45 × 30 mm, 2-layer, 3 mounting holes, USB-C bottom edge
- Status: `python3 boards/wave2/wave2gen.py irblaster-c3` → self-check OK

## BOM (bom_lcsc.csv)

| Ref | Value | Footprint | LCSC # | MPN | Qty |
|---|---|---|---|---|---|
| U1 | ESP32-C3-WROOM-02 | ESP32-C3-WROOM-02 | C2934569 | ESP32-C3-WROOM-02-N4 | 1 |
| U2 | AP2112K-3.3 | SOT-23-5 | C51118 | AP2112K-3.3TRG1 | 1 |
| U3 | TSOP38238 | custom:TSOP382xx | C2916293 | TSOP38238 | 1 |
| U4 | BH1750FVI | custom:BH1750-WSOF6 | C78955 | BH1750FVI-TR | 1 |
| Q1 | S8050 | SOT-23 | C2148 | S8050 | 1 |
| D2,D3 | TSAL6200 IR LEDs | custom:IRLED-5mm | C2895983 | TSAL6200 | 2 |
| D1 | LED red (STAT) | 0603 | C2286 | 17-21SURC/S530-A3/TR8 | 1 |
| X1 | USB-C 16P | custom:USB-C-16P-MidMount | C165948 | TYPE-C-31-M-12 | 1 |
| BT1 | SW_PUSH (BOOT) | custom:Tactile-6x6-SMD | C91808 | TS-1187A-B-A-B | 1 |
| R6,R7 | 47R (IR LED ballast) | 0603 | C23134 | 0603WAF470JT5E | 2 |
| R3,R4 | 5.1k (USB CC) | 0603 | C23186 | 0603WAF5101T5E | 2 |
| R5 | 4.7k (RX pull-up) | 0603 | C23162 | 0603WAF4701T5E | 1 |
| R2,R8 | 1k | 0603 | C21190 | 0603WAF1001T5E | 2 |
| R9 | 100R (Q1 base) | 0603 | C22775 | 0603WAF1000T5E | 1 |
| R1 | 10k (EN) | 0603 | C98252 | 0603WAF1002T5E | 1 |
| C1–C4 | 100nF | 0603 | C14663 | CL10B104KB8NNNC | 4 |
| C5 | 10uF | 0805 | C15850 | CL21A106KPFNNNE | 1 |
| J1 | Conn_01x04 (3V3/TX0/RX0/GND) | PinHeader_1x04_P2.54mm | C49241 | A2541WV-4P | 1 |

## Pinout (C3-WROOM-02)

| Signal | GPIO | Notes |
|---|---|---|
| IR_TX | GPIO4 | R9 100R → Q1 S8050 → D2/D3 (R6/R7 47R) |
| IR_RX | GPIO5 | U3 TSOP38238 out, R5 4.7k pull-up, C4 100nF |
| I2C_SDA / I2C_SCL | GPIO6 / GPIO7 | U4 BH1750 (0x23) |
| STAT_LED | GPIO10 | D1 via R8 |
| BOOT | GPIO9 | BT1 |
| USB D- / D+ | GPIO18 / GPIO19 | native USB-Serial-JTAG |
| TX0 / RX0 | GPIO21 / GPIO20 | J1 prog header |

## Firmware

See `esphome/irblaster-c3.yaml` — remote_transmitter (GPIO4, 50% carrier),
remote_receiver (GPIO5), bh1750 sensor, climate_ir example stub.

## Routing status

**v0.1 concept — signals left for autorouting.** Power rails routed
(VBUS/+3V3/GND + stitching); IR_TX/IR_RX/I2C/USB signals unrouted.

## Analyzer notes

`analyze_pcb.py`: **DFM-001 = 0**. RT-001 unrouted errors expected.
BH1750 WSOF6 footprint uses 0.95 mm pitch (was fixed from 0.5 mm draft).

## Caveats (verify before fabrication!)

- IR LED current: 47R ballasts give ~40–60 mA pulse per LED from 5 V —
  check S8050 SOA and duty cycle for long NEC bursts; reduce if needed.
- TSOP38238 supply filter (R/C per datasheet) recommended before fab.
- **Verify all footprints, pin numbers, and clearances against KiCad
  libraries + datasheets before ordering boards.**

## Renders

| Raytraced 3D (KiCad) | 2D layout |
|---|---|
|  |  |
|  |  |

🎬 24 real KiCad raytraced frames stitched with ffmpeg (tools/turntable.sh).

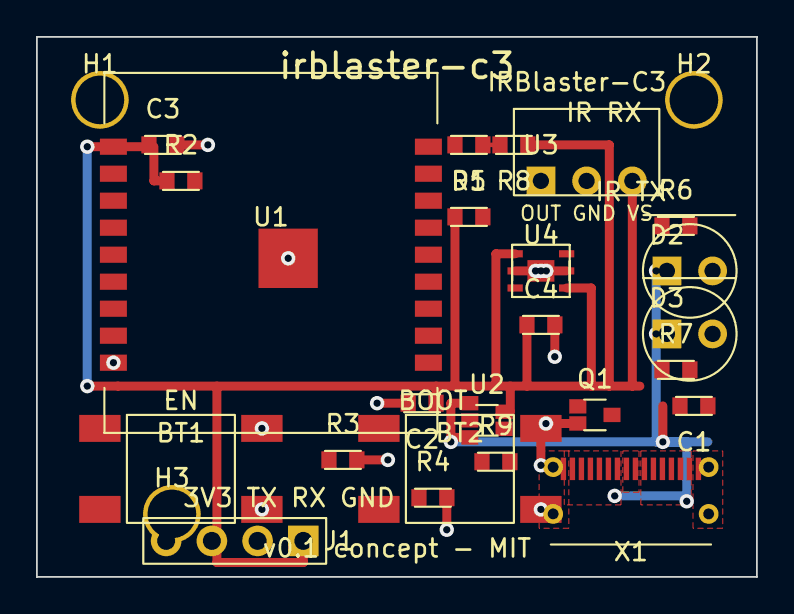
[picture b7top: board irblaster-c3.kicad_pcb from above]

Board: 2 copper layers, 40.0 x 30.0 mm, 27 parts (0 on the bottom side), 20 nets.

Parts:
BT1, BT2: SW_PUSH; Tactile-6x6-SMD
C1, C2: 10uF; C_0603_1608Metric
C3, C4: 100nF; C_0603_1608Metric
D1: LED_GRN; LED_0603_1608Metric
D2, D3: TSAL6200; IR-LED-5mm
H1, H2, H3: MountingHole_M2.5
J1: Conn_01x04; PinHeader_1x04_P2.54mm_Vertical
Q1: S8050; SOT-23
R2: 10k; R_0603_1608Metric
R3, R4: 5.1k; R_0603_1608Metric
R5: 4.7k; R_0603_1608Metric
R6, R7: 47R; R_0603_1608Metric
R8: 1k; R_0603_1608Metric
R9: 100R; R_0603_1608Metric
U1: ESP32-C3-WROOM-02
U2: AP2112K-3.3; SOT-23-5
U3: TSOP38238
U4: BH1750; BH1750-WSOF6
X1: USB_C_16P; USB_C_Receptacle_USB2.0_16P

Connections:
+3V3: C2.1, C3.1, C4.1, J1.1, R2.1, R5.1, R8.1, U1.1, U2.5, U3.3, U4.1, U4.6
BOOT: BT1.1, BT1.3, BT2.1, BT2.3, U1.8
EN: R2.2, U1.2
GND: BT1.2, BT1.4, BT2.2, BT2.4, C1.2, C2.2, C3.2, C4.2, J1.4, Q1.2, R3.2, R4.2, U1.9, U1.19, U2.2, U3.2, U4.2, U4.5, U4.7, X1.1, X1.8, X1.9, X1.16, X1.S1, X1.S2, X1.S3, X1.S4
IR2_K: D2.2, D3.2, R7.1
IR_C: Q1.3, R6.2, R7.2
IR_DRV: Q1.1, R9.2
IR_RX: R5.2, U1.4, U3.1
IR_TX: R9.1, U1.3
LED1_A: D1.1, R8.2
RX0: J1.3, U1.11
SCL: U1.6, U4.3
SDA: U1.5, U4.4
STAT_LED: D1.2, U1.10
TX0: J1.2, U1.12
USB_CC1: R3.1, X1.3
USB_CC2: R4.1, X1.14
USB_DM: U1.13, X1.5, X1.12
USB_DP: U1.14, X1.4, X1.13
VBUS: C1.1, D2.1, D3.1, U2.1, U2.3, X1.2, X1.7, X1.10, X1.15

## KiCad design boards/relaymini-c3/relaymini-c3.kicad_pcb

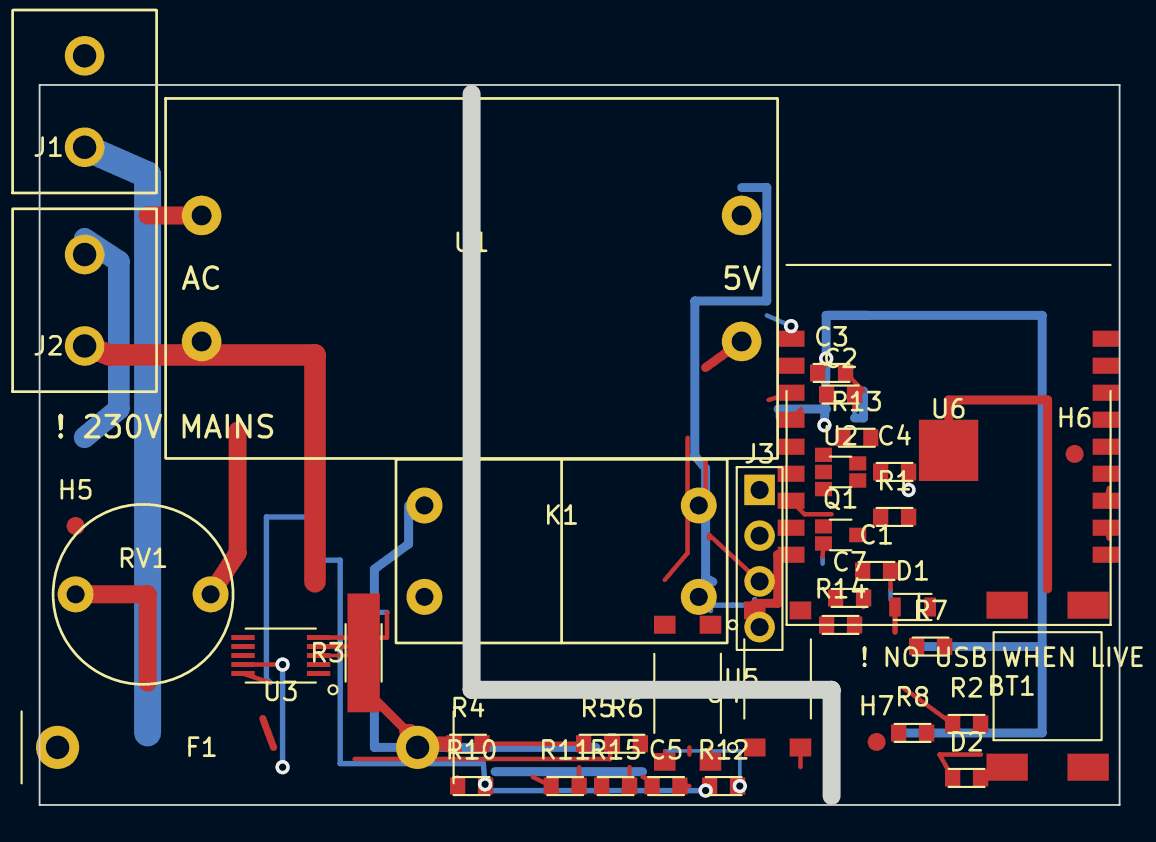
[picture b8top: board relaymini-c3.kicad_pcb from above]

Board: 2 copper layers, 60.0 x 40.0 mm, 39 parts (0 on the bottom side), 24 nets.

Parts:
BT1: SW_PUSH; Tactile-6x6-SMD
C1, C3: 10uF; C_0603_1608Metric
C2, C4, C5, C7: 100nF; C_0603_1608Metric
D1: 1N4148WS; D_SOD-323
D2: LED_GRN; LED_0603_1608Metric
F1: FUSE_10A; FuseClip-5x20
H5, H6, H7: Fiducial; Fiducial_1mm
J1, J2: Term_5.08_2P; TerminalBlock-5.08-2P
J3: Conn_01x04; PinHeader_1x04_P2.54mm_Vertical
K1: HF32F-G
Q1: S8050; SOT-23
R1, R2, R12, R14: 1k; R_0603_1608Metric
R3: 1mR; Shunt-2512
R4, R5: 470k; R_0603_1608Metric
R6: 270R; R_0603_1608Metric
R7, R8, R10, R11, R13, R15: 10k; R_0603_1608Metric
RV1: MOV_10D471K; MOV-10D
U1: HLK-PM01
U2: AP2112K-3.3; SOT-23-5
U3: BL0942; BL0942-SSOP10
U4, U5: PC817; PC817-SOP4
U6: ESP32-C3-WROOM-02

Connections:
+3V3: C2.1, C3.1, C4.1, J3.1, R7.1, R8.1, R13.1, U2.5, U6.1
+5V: C1.1, D1.2, K1.3, U1.3, U2.1, U2.3
+5V_AC: C5.1, R10.1, R11.1, R15.1, U3.1
AC_L_F: F1.1, R3.2, R4.1, RV1.1, U1.1, U3.2
AC_L_SW: J1.1, J2.1, K1.2
AC_N: J1.2, J2.2, RV1.2, U1.2
BTN: BT1.1, BT1.3, R8.2, U6.8
COIL: D1.1, K1.4, Q1.3
EN: C7.1, R7.2, U6.2
GND: BT1.2, BT1.4, C1.2, C2.2, C3.2, C4.2, C7.2, D2.2, J3.4, Q1.2, U1.4, U2.2, U4.2, U5.2, U6.9, U6.19
GND_AC: C5.2, K1.1, R3.1, R6.2, U3.3, U3.5, U4.3, U5.3
LED_A: D2.1, R2.2
MTR_RX: R13.2, U6.3
MTR_RX_AC: R11.2, R15.2, U3.9, U4.4, U5.4
MTR_TX: R14.1, U6.4
MTR_TX_AC: R10.2, R12.1, U3.10
Q1B: Q1.1, R1.2
RELAY: R1.1, U6.5
RX0: J3.3, U6.11
STAT_LED: R2.1, U6.7
TX0: J3.2, U6.12
U5_A: R14.2, U4.1, U5.1
VD_A: R4.2, R5.1
VSENSE: R5.2, R6.1, U3.4
